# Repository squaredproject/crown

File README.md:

# Crown

This is all the code relating to the Crown burning man project of 2018.

## Crown

The Crown subdirectory is the Processing model for light control. Processing demands the name
of the directory is Crown, so Crown it is.

## model

Various design models

testing testing

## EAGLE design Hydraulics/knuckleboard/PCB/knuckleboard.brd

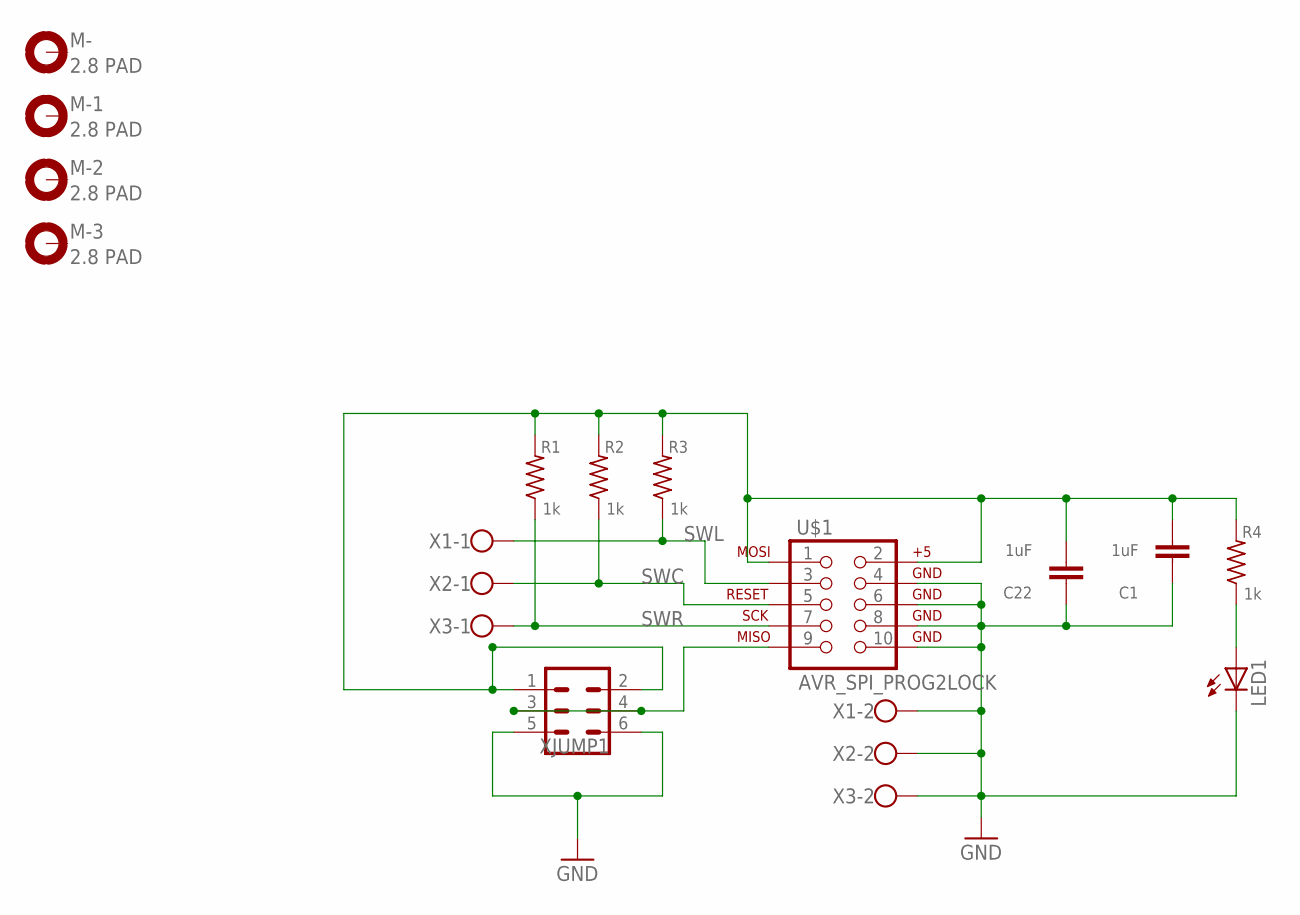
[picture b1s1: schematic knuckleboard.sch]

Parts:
C1, C22: 1uF; C1206
LED1: LEDCHIPLED_1206; CHIPLED_1206
M-, M-1, M-2, M-3: 2.8 PAD; 2,8-PAD
R1, R2, R3, R4: 1k; M1206
U$1: AVR_SPI_PROG2LOCK; 2X5-SHROUDED_LOCK
X1, X2, X3: W237-102
XJUMP1: MA03-2

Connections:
GND: C1.1, C22.1, LED1.C, U$1.4, U$1.6, U$1.8, U$1.10, X1.2, X2.2, X3.2, XJUMP1.5, XJUMP1.6
unnamed: LED1.A, R4.1
unnamed: U$1.9, XJUMP1.3, XJUMP1.4
SWC: R2.1, U$1.5, X2.1
SWL: R3.1, U$1.3, X1.1
SWR: R1.1, U$1.7, X3.1
VDD5V: C1.2, C22.2, R1.2, R2.2, R3.2, R4.2, U$1.1, U$1.2, XJUMP1.1, XJUMP1.2

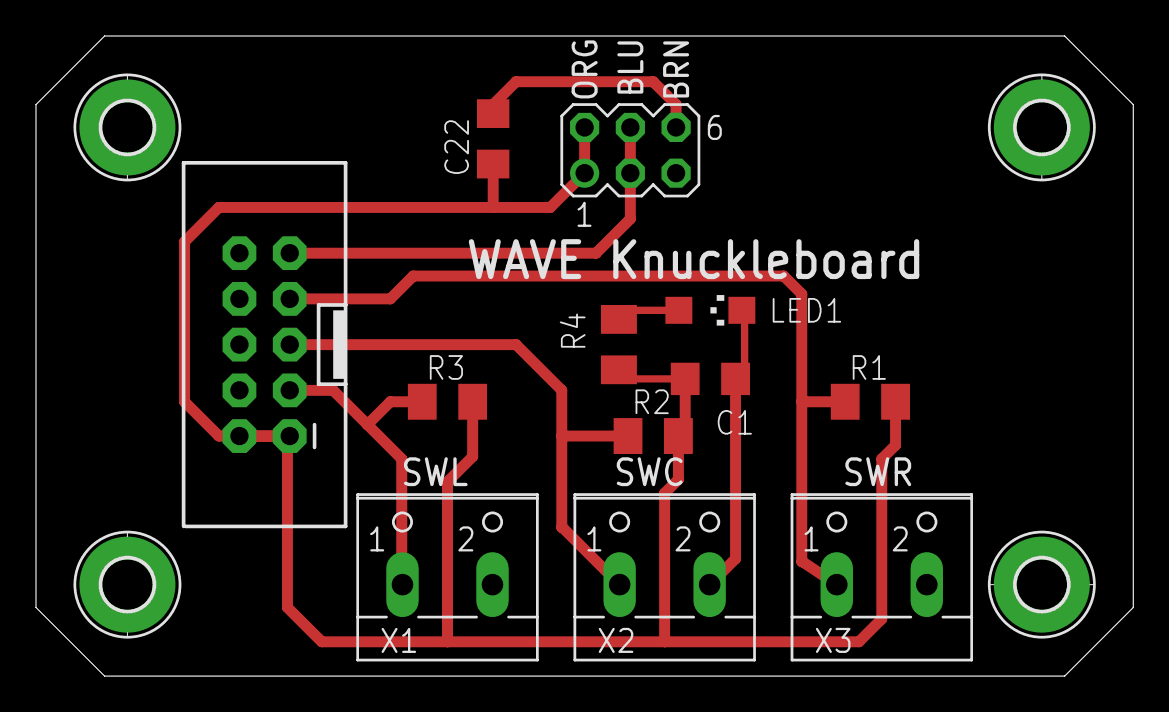
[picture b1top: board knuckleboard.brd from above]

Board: 2 copper layers, 61.0 x 35.6 mm, 16 parts (0 on the bottom side), 7 nets.

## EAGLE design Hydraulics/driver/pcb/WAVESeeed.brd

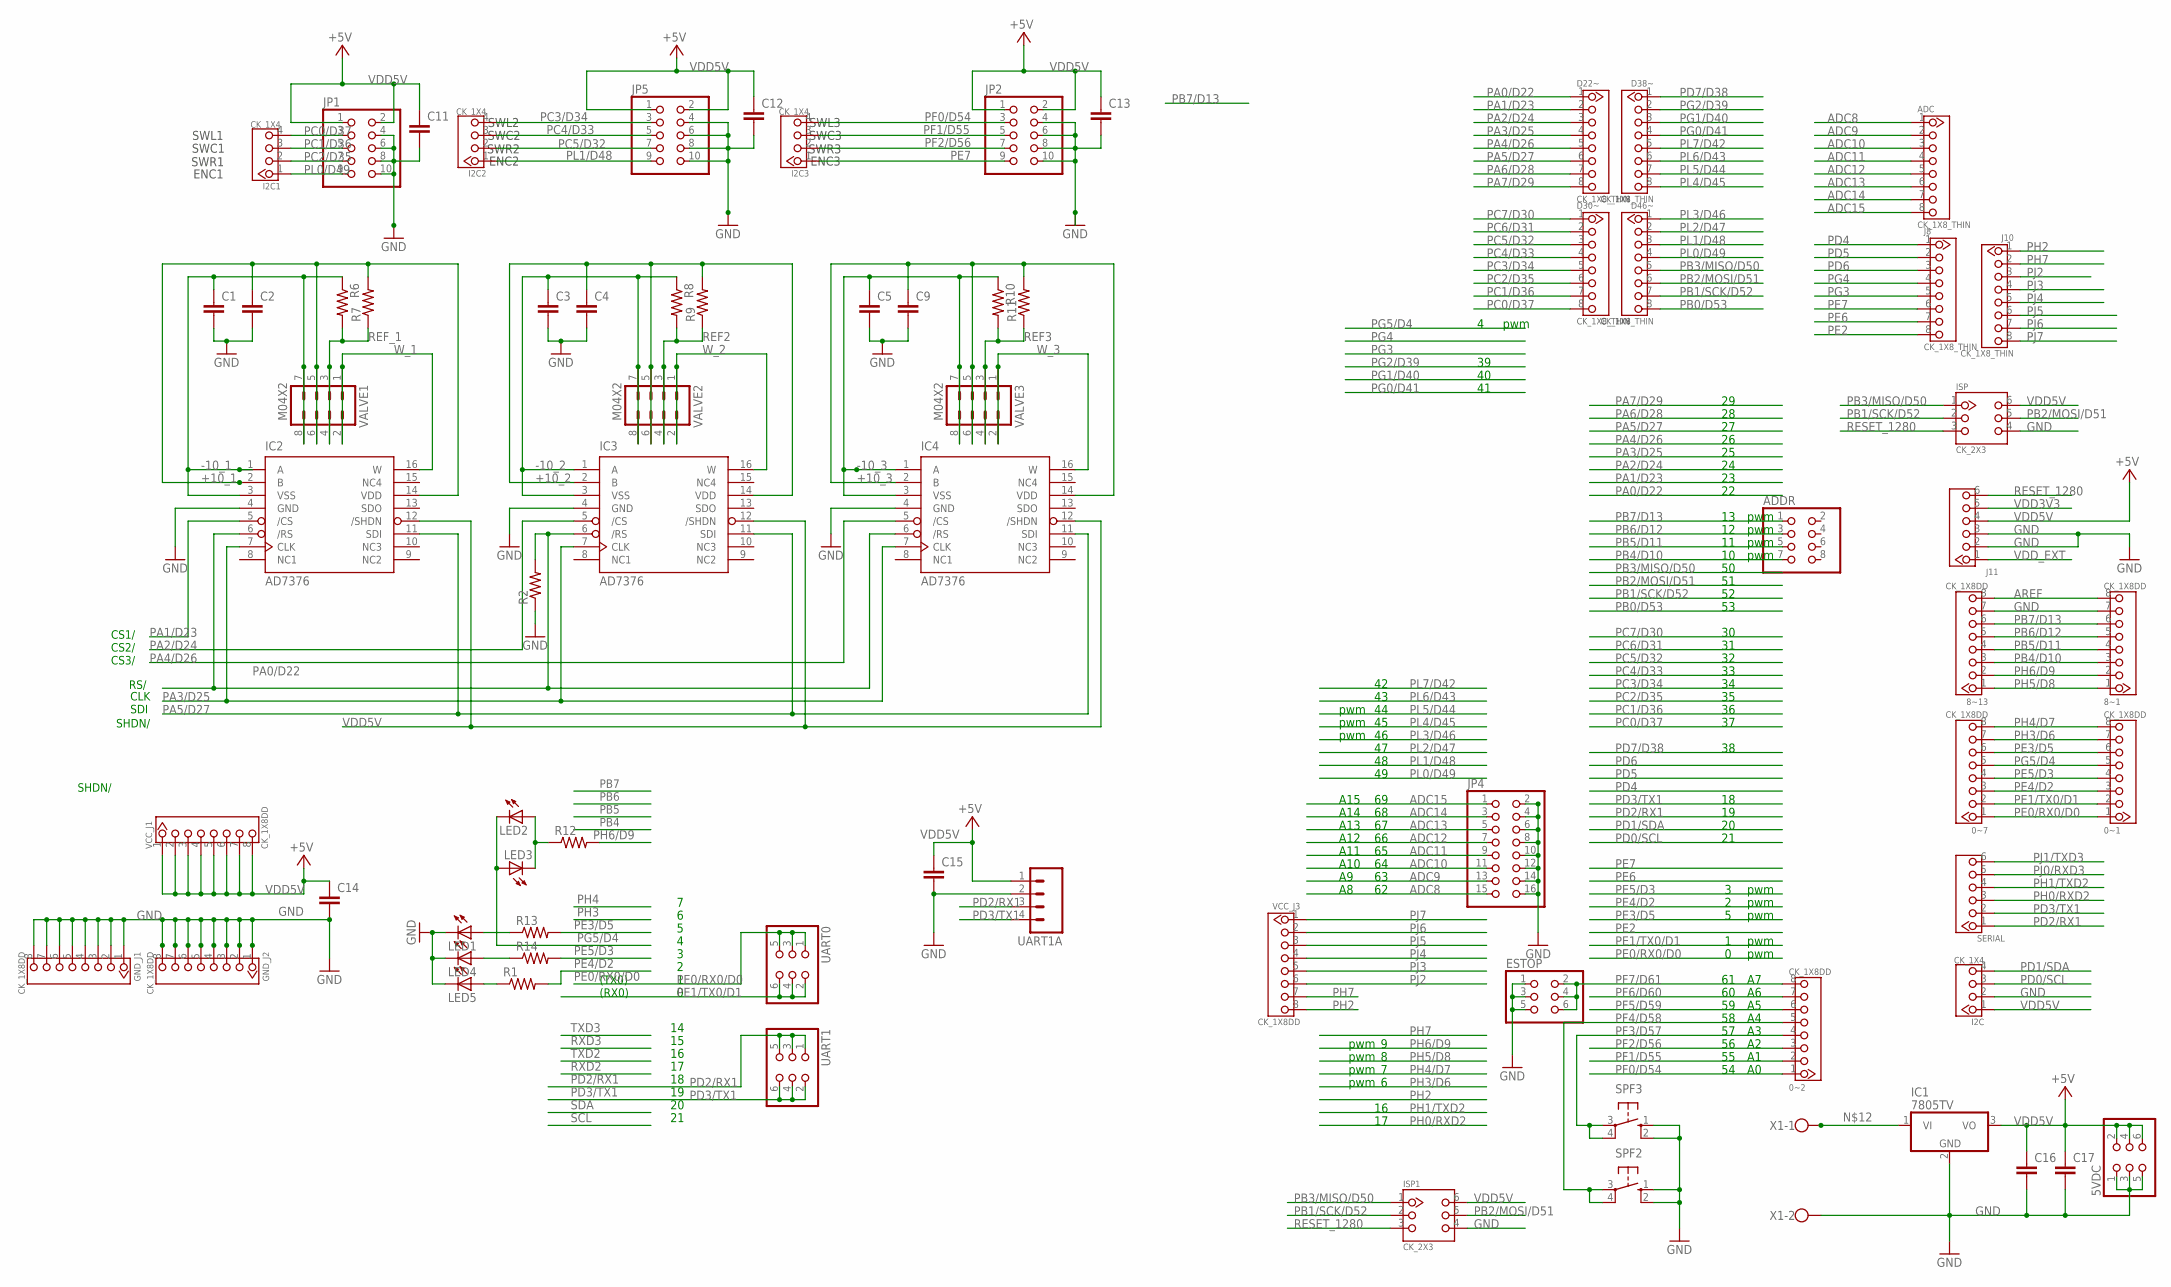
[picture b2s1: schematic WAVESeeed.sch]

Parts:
0~1, 0~2, 0~7, 8~1, 8~13: CK_1X8DD; CK_1X8
5VDC: PINHD-2X3; 2X03
ADC: CK_1X8_THIN
ADDR: PINHD-2X4; 2X04
C1, C2, C3, C4, C5, C9, C11, C15, C16: C-EUC1206; C1206
C12, C13, C14, C17: C-EUC1206K; C1206K
D22~, D30~, D38~, D46~: CK_1X8_THIN
ESTOP: PINHD-2X3; 2X03
GND_J1, GND_J2: CK_1X8DD; CK_1X8
I2C, I2C1, I2C2, I2C3: CK_1X4
IC1: 7805TV; TO220V
IC2, IC3, IC4: AD7376; SO-16W
ISP, ISP1: CK_2X3; CK_2X3_THIN
J8, J10: CK_1X8_THIN
J11: CK_1X6
JP1, JP2, JP5: PINHD-2X5; 2X05
JP4: PINHD-2X8; 2X08
LED1, LED2, LED3, LED4, LED5: LEDCHIPLED_1206; CHIPLED_1206
R1, R2, R12, R13, R14: R-US_R1206; R1206
R6, R7, R8, R9, R10, R11: R-US_M1206; M1206
SERIAL: CK_1X6
SPF2, SPF3: 10-XX; B3F-10XX
UART0, UART1: PINHD-2X3; 2X03
UART1A: M04PTH; 1X04
VALVE1, VALVE2, VALVE3: M04X2; 2X4
VCC_J1, VCC_J3: CK_1X8DD; CK_1X8
X1: W237-102

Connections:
+10_1: C2.1, IC2.2 (B), IC2.14 (VDD), R7.2, VALVE1.5, VALVE1.6
+10_2: C4.1, IC3.2 (B), IC3.14 (VDD), R9.2, VALVE2.5, VALVE2.6
+10_3: C9.1, IC4.2 (B), IC4.14 (VDD), R11.2, VALVE3.5, VALVE3.6
-10_1: C1.1, IC2.1 (A), IC2.3 (VSS), R6.1, VALVE1.7, VALVE1.8
-10_2: C3.1, IC3.1 (A), IC3.3 (VSS), R8.1, VALVE2.7, VALVE2.8
-10_3: C5.1, IC4.1 (A), IC4.3 (VSS), R10.1, VALVE3.7, VALVE3.8
ADC8: ADC.1, JP4.15
ADC9: ADC.2, JP4.13
ADC10: ADC.3, JP4.11
ADC11: ADC.4, JP4.9
ADC12: ADC.5, JP4.7
ADC13: ADC.6, JP4.5
ADC14: ADC.7, JP4.3
ADC15: ADC.8, JP4.1
AREF: 8~1.8, 8~13.8
GND: 5VDC.1, 5VDC.3, 5VDC.5, 8~1.7, 8~13.7, C1.2, C2.2, C3.2, C4.2, C5.2, C9.2, C11.2, C12.2, C13.2, C14.2, C15.2, C16.2, C17.2, ESTOP.1, ESTOP.3, ESTOP.5, GND_J1.1, GND_J1.2, GND_J1.3, GND_J1.4, GND_J1.5, GND_J1.6, GND_J1.7, GND_J1.8, GND_J2.1, GND_J2.2, GND_J2.3, GND_J2.4, GND_J2.5, GND_J2.6, GND_J2.7, GND_J2.8, I2C.2, IC1.2 (GND), IC2.4 (GND), IC3.4 (GND), IC4.4 (GND), ISP.4, ISP1.4, J11.2, J11.3, JP1.4, JP1.6, JP1.8, JP1.10, JP2.4, JP2.6, JP2.8, JP2.10, JP4.2, JP4.4, JP4.6, JP4.8, JP4.10, JP4.12, JP4.14, JP4.16, JP5.4, JP5.6, JP5.8, JP5.10, LED1.C, LED4.C, LED5.C, R2.1, SPF2.1 (S), SPF2.2 (S1), SPF3.1 (S), SPF3.2 (S1), UART1A.2, X1.2
unnamed: LED2.A, LED3.C, R12.1
unnamed: LED1.A, R13.1
unnamed: LED5.A, R1.1
unnamed: LED4.A, R14.1
unnamed: IC1.1 (VI), X1.1
PA0/D22: D22~.1, IC2.6 (/RS), IC3.6 (/RS), IC4.6 (/RS), R2.2
PA1/D23: D22~.2, IC2.5 (/CS)
PA2/D24: D22~.3, IC3.5 (/CS)
PA3/D25: D22~.4, IC2.7 (CLK), IC3.7 (CLK), IC4.7 (CLK)
PA4/D26: D22~.5, IC4.5 (/CS)
PA5/D27: D22~.6, IC2.11 (SDI), IC3.11 (SDI), IC4.11 (SDI)
PA6/D28: D22~.7
PA7/D29: D22~.8
PB0/D53: D46~.8
PB1/SCK/D52: D46~.7, ISP.2, ISP1.2
PB2/MOSI/D51: D46~.6, ISP.5, ISP1.5
PB3/MISO/D50: D46~.5, ISP.1, ISP1.1
PB4/D10: 8~1.3, 8~13.3, ADDR.7
PB5/D11: 8~1.4, 8~13.4, ADDR.5
PB6/D12: 8~1.5, 8~13.5, ADDR.3
PB7/D13: 8~1.6, 8~13.6, ADDR.1
PC0/D37: D30~.8, I2C1.4, JP1.3
PC1/D36: D30~.7, I2C1.3, JP1.5
PC2/D35: D30~.6, I2C1.2, JP1.7
PC3/D34: D30~.5, I2C2.4, JP5.3
PC4/D33: D30~.4, I2C2.3, JP5.5
PC5/D32: D30~.3, I2C2.2, JP5.7
PC6/D31: D30~.2
PC7/D30: D30~.1
PD0/SCL: I2C.3
PD1/SDA: I2C.4
PD2/RX1: SERIAL.1, UART1.1, UART1.3, UART1.5, UART1A.3
PD3/TX1: SERIAL.2, UART1.2, UART1.4, UART1.6, UART1A.4
PD4: J8.1
PD5: J8.2
PD6: J8.3
PD7/D38: D38~.1
PE0/RX0/D0: 0~1.1, 0~7.1, UART0.1, UART0.3, UART0.5
PE1/TX0/D1: 0~1.2, 0~7.2, UART0.2, UART0.4, UART0.6
PE2: J8.8
PE3/D5: 0~1.6, 0~7.6, R13.2
PE4/D2: 0~1.3, 0~7.3, R1.2
PE5/D3: 0~1.4, 0~7.4, R14.2
PE6: J8.7
PE7: I2C3.1, J8.6, JP2.9
PF0/D54: 0~2.1, I2C3.4, JP2.3
PF1/D55: 0~2.2, I2C3.3, JP2.5
PF2/D56: 0~2.3, I2C3.2, JP2.7
PF3/D57: 0~2.4, SPF3.3, SPF3.4 (P1)
PF4/D58: 0~2.5, SPF2.3, SPF2.4 (P1)
PF5/D59: 0~2.6
PF6/D60: 0~2.7
PF7/D61: 0~2.8, ESTOP.2, ESTOP.4, ESTOP.6
PG0/D41: D38~.4
PG1/D40: D38~.3
PG2/D39: D38~.2
PG3: J8.5
PG4: J8.4
PG5/D4: 0~1.5, 0~7.5, LED2.C, LED3.A
PH0/RXD2: SERIAL.3
PH1/TXD2: SERIAL.4
PH2: J10.1, VCC_J3.8
PH3/D6: 0~1.7, 0~7.7
PH4/D7: 0~1.8, 0~7.8
PH5/D8: 8~1.1, 8~13.1
PH6/D9: 8~1.2, 8~13.2, R12.2
PH7: J10.2, VCC_J3.7
PJ0/RXD3: SERIAL.5
PJ1/TXD3: SERIAL.6
PJ2: J10.3, VCC_J3.6
PJ3: J10.4, VCC_J3.5
PJ4: J10.5, VCC_J3.4
PJ5: J10.6, VCC_J3.3
PJ6: J10.7, VCC_J3.2
PJ7: J10.8, VCC_J3.1
PL0/D49: D46~.4, I2C1.1, JP1.9
PL1/D48: D46~.3, I2C2.1, JP5.9
PL2/D47: D46~.2
PL3/D46: D46~.1
PL4/D45: D38~.8
PL5/D44: D38~.7
PL6/D43: D38~.6
PL7/D42: D38~.5
REF2: R8.2, R9.1, VALVE2.3, VALVE2.4
REF3: R10.2, R11.1, VALVE3.3, VALVE3.4
REF_1: R6.2, R7.1, VALVE1.3, VALVE1.4
RESET_1280: ISP.3, ISP1.3, J11.6
VDD3V3: J11.5
VDD5V: 5VDC.2, 5VDC.4, 5VDC.6, C11.1, C12.1, C13.1, C14.1, C15.1, C16.1, C17.1, I2C.1, IC1.3 (VO), IC2.12 (/SHDN), IC3.12 (/SHDN), IC4.12 (/SHDN), ISP.6, ISP1.6, J11.4, JP1.1, JP1.2, JP2.1, JP2.2, JP5.1, JP5.2, UART1A.1, VCC_J1.1, VCC_J1.2, VCC_J1.3, VCC_J1.4, VCC_J1.5, VCC_J1.6, VCC_J1.7, VCC_J1.8
VDD_EXT: J11.1
W_1: IC2.16 (W), VALVE1.1, VALVE1.2
W_2: IC3.16 (W), VALVE2.1, VALVE2.2
W_3: IC4.16 (W), VALVE3.1, VALVE3.2

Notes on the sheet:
pwm
A10
A11
A12
A13
A14
A15
SWL1
SWC1
SWR1
ENC1
SWL2
SWC2
SWR2
ENC2
SWL3
SWC3
SWR3
ENC3
CS2/
CS3/
SDI
CLK
CS1/
SHDN/
(TX0)
(RX0)
RS/

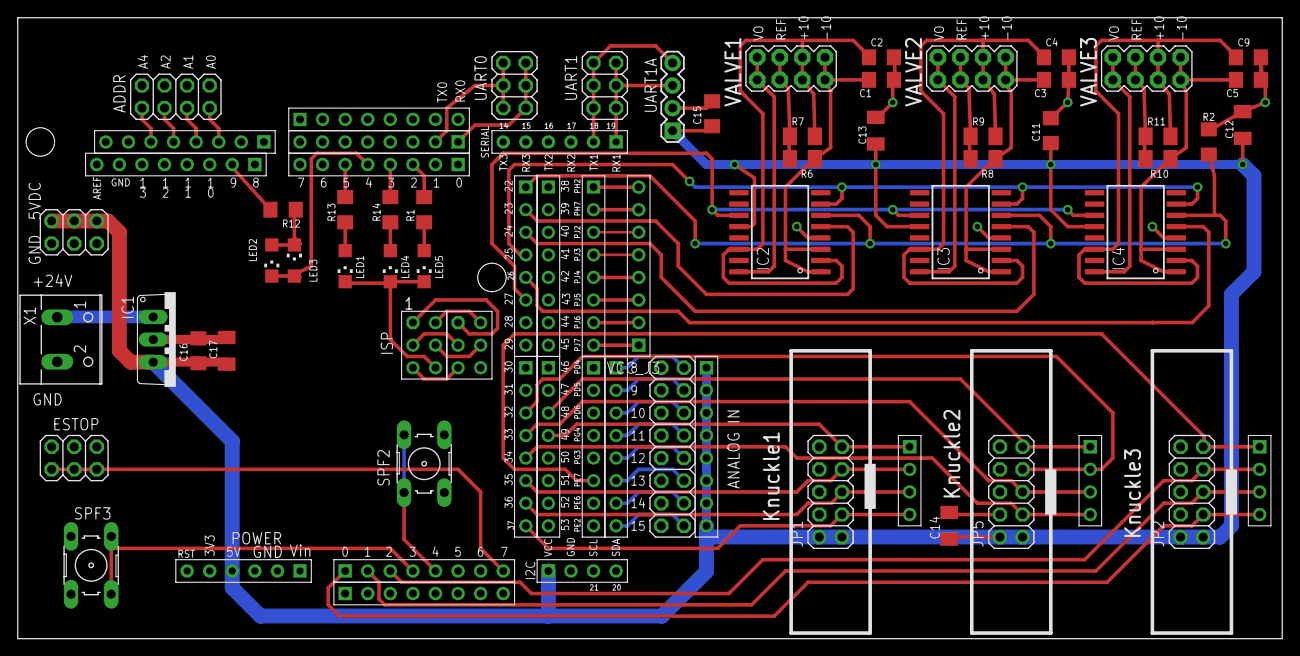
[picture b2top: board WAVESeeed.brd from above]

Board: 2 copper layers, 142.2 x 69.8 mm, 73 parts (0 on the bottom side), 77 nets.

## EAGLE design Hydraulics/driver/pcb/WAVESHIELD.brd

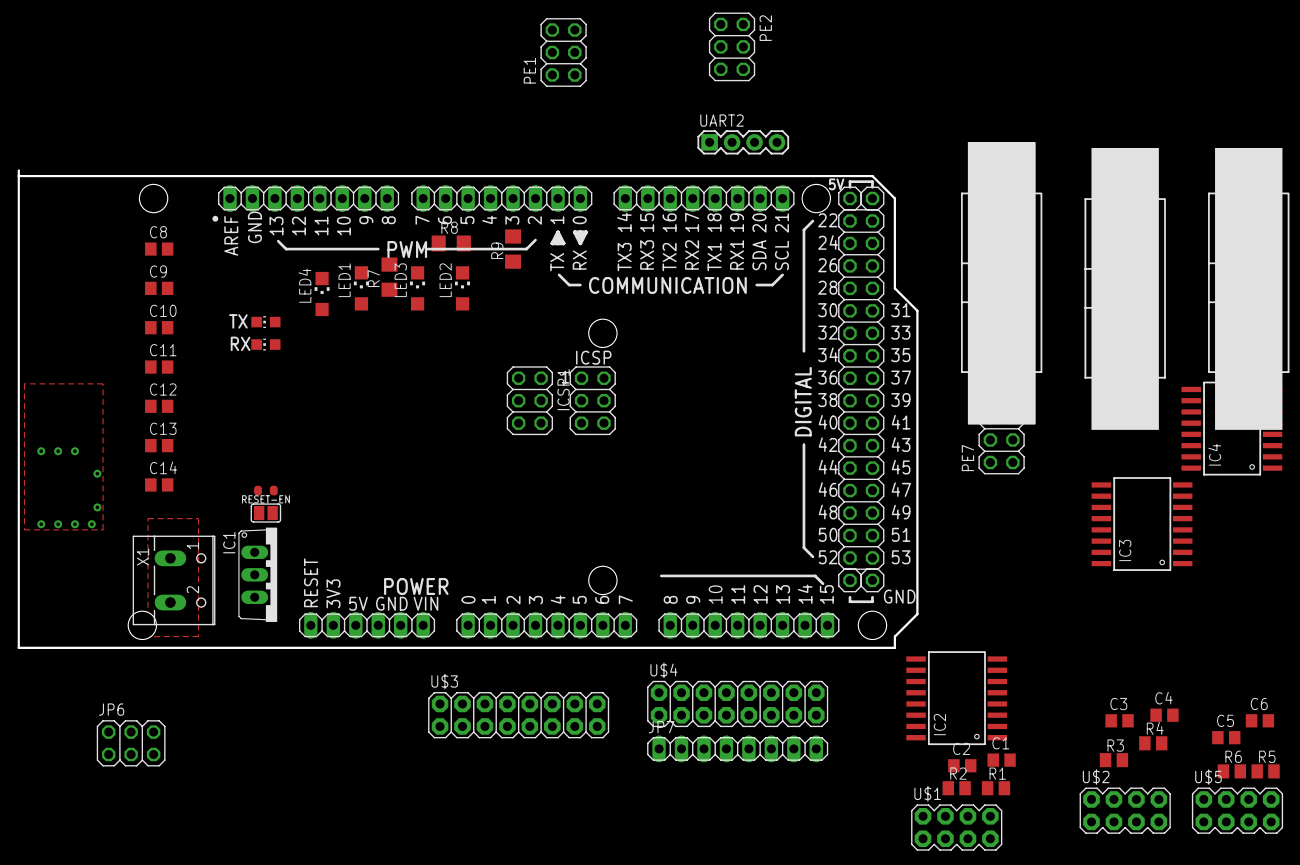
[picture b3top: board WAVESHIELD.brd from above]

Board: 2 copper layers, 101.6 x 54.0 mm, 64 parts (1 on the bottom side), 63 nets.

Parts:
C1, C2, C3, C4, C5, C6, C8, C9, C10, C11, C12, C13, C14: C0805
C7: 100n; C0603-ROUND
COMMUNICATION: 1X08
IC1: 7805TV; TO220V
IC2, IC3, IC4: AD7376; SO-16W
ICSP, ICSP1: ICSP; 2X03
JP1, JP2, JP3, JP4: 1X01
JP6: 2X03
JP7: 1X08
KNUCK1, KNUCK2, KNUCK3: M05X2SHD_LOCK; 2X5-SHROUDED_LOCK
LED1, LED2, LED3, LED4: CHIPLED_1206
PE1, PE2, PE7: 2X03
PORTF: 1X08
PORTL: 1X08
POWER: 1X06
PWMH: 1X08
PWML: 1X08
R1, R2, R3, R4, R5, R6: M0805
R7, R8, R9: R1206
RESET-EN: SJ
RX: YELLOW; CHIP-LED0805
TX: YELLOW; CHIP-LED0805
U$1, U$2, U$5: M04X2; 2X4
U$3, U$4: M08X2; 2X8
UART2: 1X04
UBOOT: SJ
X1: W237-102
XIOH: 2X08
XIOL: 2X08

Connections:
+5V: C8.1, C9.1, C10.1, C12.1, C13.1, IC1.3, ICSP.2, ICSP1.2, JP1.1, JP2.1, JP7.1, JP7.2, JP7.3, JP7.4, JP7.5, JP7.6, JP7.7, JP7.8, KNUCK1.1, KNUCK1.2, KNUCK2.1, KNUCK2.2, KNUCK3.1, KNUCK3.2, POWER.3
ADC8: PORTL.1, U$4.2
ADC9: PORTL.2, U$4.4
ADC10: PORTL.3, U$4.6
ADC11: PORTL.4, U$4.8
ADC12: PORTL.5, U$4.10
ADC13: PORTL.6, U$4.12
ADC14: PORTL.7, U$4.14
ADC15: PORTL.8, U$4.16
DTR: C7.1, UBOOT.1
GND: C1.2, C2.2, C3.2, C4.2, C5.2, C6.2, C8.2, C10.2, C12.2, C13.2, IC1.2, IC2.4, IC3.4, IC4.4, ICSP.6, ICSP1.6, JP3.1, JP4.1, KNUCK1.4, KNUCK1.6, KNUCK1.8, KNUCK1.10, KNUCK2.4, KNUCK2.6, KNUCK2.8, KNUCK2.10, KNUCK3.4, KNUCK3.6, KNUCK3.8, KNUCK3.10, LED1.C, LED4.C, PE7.1, PE7.3, PE7.5, POWER.4, POWER.5, PWMH.7, U$3.2, U$3.4, U$3.6, U$3.8, U$3.10, U$3.12, U$3.14, U$3.16, U$4.15, UART2.2, UBOOT.2, X1.2
unnamed: LED2.A, LED3.C, R7.1
unnamed: LED1.A, R8.1
unnamed: LED4.A, R9.1
unnamed: PE1.2, PE1.4, PE1.6
unnamed: C1.1, IC2.1, IC2.3, R1.1, U$1.7, U$1.8
unnamed: IC1.1, X1.1
unnamed: R1.2, R2.1, U$1.3, U$1.4
unnamed: IC2.16, U$1.1, U$1.2
unnamed: C3.1, IC3.1, IC3.3, R3.1, U$2.7, U$2.8
unnamed: C4.1, IC3.2, R4.2, U$2.5, U$2.6
unnamed: R3.2, R4.1, U$2.3, U$2.4
unnamed: IC3.16, U$2.1, U$2.2
unnamed: C5.1, IC4.1, IC4.3, R5.1, U$5.7, U$5.8
unnamed: C6.1, IC4.2, R6.2, U$5.5, U$5.6
unnamed: R5.2, R6.1, U$5.3, U$5.4
unnamed: IC4.16, U$5.1, U$5.2
PA0: IC2.12, IC3.12, IC4.12, XIOH.16
PA1: IC2.5, XIOH.15
PA2: IC3.5, XIOH.14
PA3: IC2.7, IC3.7, IC4.7, XIOH.13
PA4: IC4.5, XIOH.12
PA5: IC2.11, IC3.11, IC4.11, XIOH.11
PB1: ICSP.3, ICSP1.3, XIOL.2
PB2: ICSP.4, ICSP1.4, XIOL.3
PB3: ICSP.1, ICSP1.1, XIOL.4
PC0: KNUCK1.3, XIOH.1
PC1: KNUCK1.5, XIOH.2
PC2: KNUCK1.7, XIOH.3
PC3: KNUCK2.3, XIOH.4
PC4: KNUCK2.5, XIOH.5
PC5: KNUCK2.7, XIOH.6
PE1: PE1.1, PE1.3, PE1.5, PWML.2
PE3: PWML.6, R8.2
PE5: PWML.4, R9.2
PE7/ICP3: KNUCK3.9, PE7.2, PE7.4, PE7.6
PF0: KNUCK3.3, PORTF.1, U$3.1
PF1: KNUCK3.5, PORTF.2, U$3.3
PF2: KNUCK3.7, PORTF.3, U$3.5
PF3: PORTF.4, U$3.7
PF4: PORTF.5, U$3.9
PF5: PORTF.6, U$3.11
PF6: PORTF.7, U$3.13
PF7: PORTF.8, U$3.15
PG5: LED2.C, LED3.A, PWML.5
PH6: PWMH.2, R7.2
PL0: KNUCK1.9, XIOL.5
PL1: KNUCK2.9, XIOL.6
RESET: C7.2, ICSP.5, ICSP1.5, POWER.1, RESET-EN.1, RESET-EN.2
RXD1: COMMUNICATION.3, PE2.2, PE2.4, PE2.6
TXD1: COMMUNICATION.4, PE2.1, PE2.3, PE2.5, UART2.3
VALVE1: C2.1, IC2.2, IC2.14, R2.2, U$1.5, U$1.6
VDD: IC3.14, IC4.14

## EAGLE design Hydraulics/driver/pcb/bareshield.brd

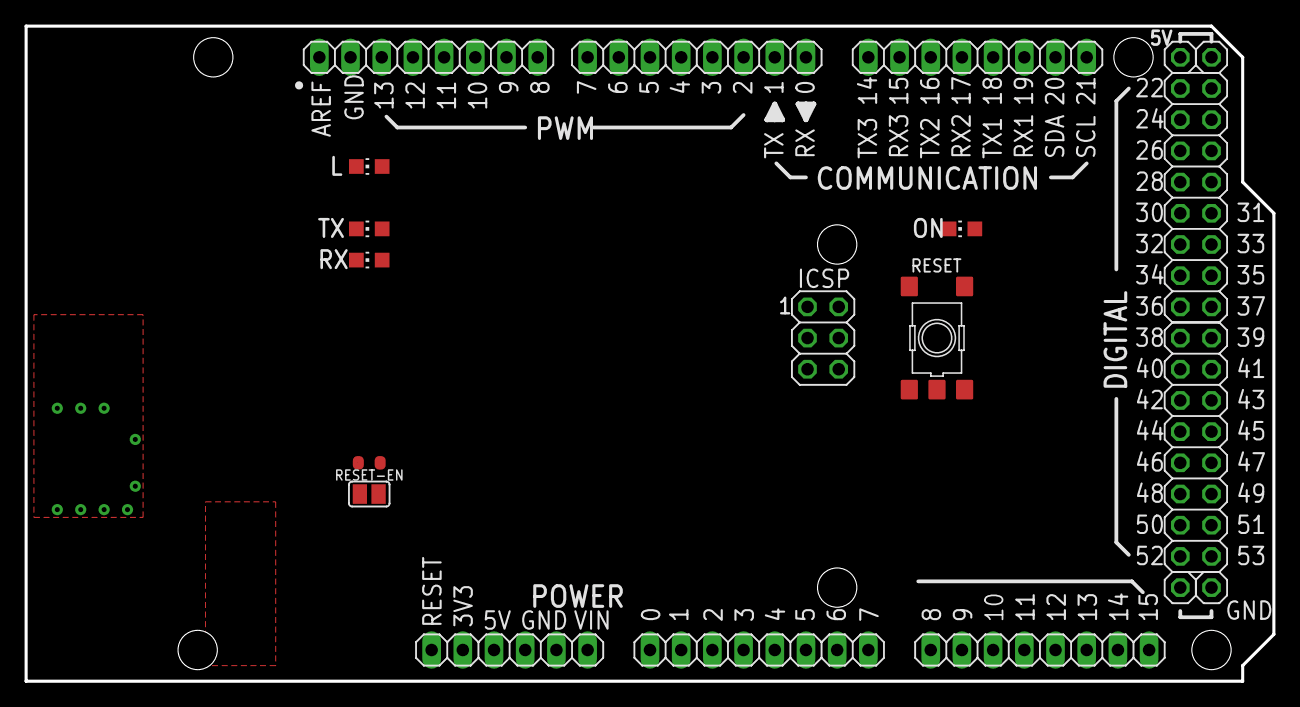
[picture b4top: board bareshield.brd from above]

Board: 2 copper layers, 101.6 x 53.3 mm, 21 parts (1 on the bottom side), 7 nets.

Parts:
ADCH: 1X08
ADCL: 1X08
C7: 100n; C0603-ROUND
COMMUNICATION: 1X08
ICSP: ICSP; 2X03
JP1, JP2, JP3, JP4: 1X01
L: YELLOW; CHIP-LED0805
ON: GREEN; CHIP-LED0805
POWER: 1X06
PWMH: 1X08
PWML: 1X08
RESET: TS42
RESET-EN: SJ
RX: YELLOW; CHIP-LED0805
TX: YELLOW; CHIP-LED0805
UBOOT: SJ
XIOH: 2X08
XIOL: 2X08

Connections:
+5V: ICSP.2, JP1.1, JP2.1, POWER.3
DTR: C7.1, UBOOT.1
GND: ICSP.6, JP3.1, JP4.1, L.C, ON.C, POWER.4, POWER.5, PWMH.7, RESET.1, RESET.2, UBOOT.2
PB1: ICSP.3, XIOL.2
PB2: ICSP.4, XIOL.3
PB3: ICSP.1, XIOL.4
RESET: C7.2, ICSP.5, POWER.1, RESET.3, RESET.4, RESET-EN.1, RESET-EN.2

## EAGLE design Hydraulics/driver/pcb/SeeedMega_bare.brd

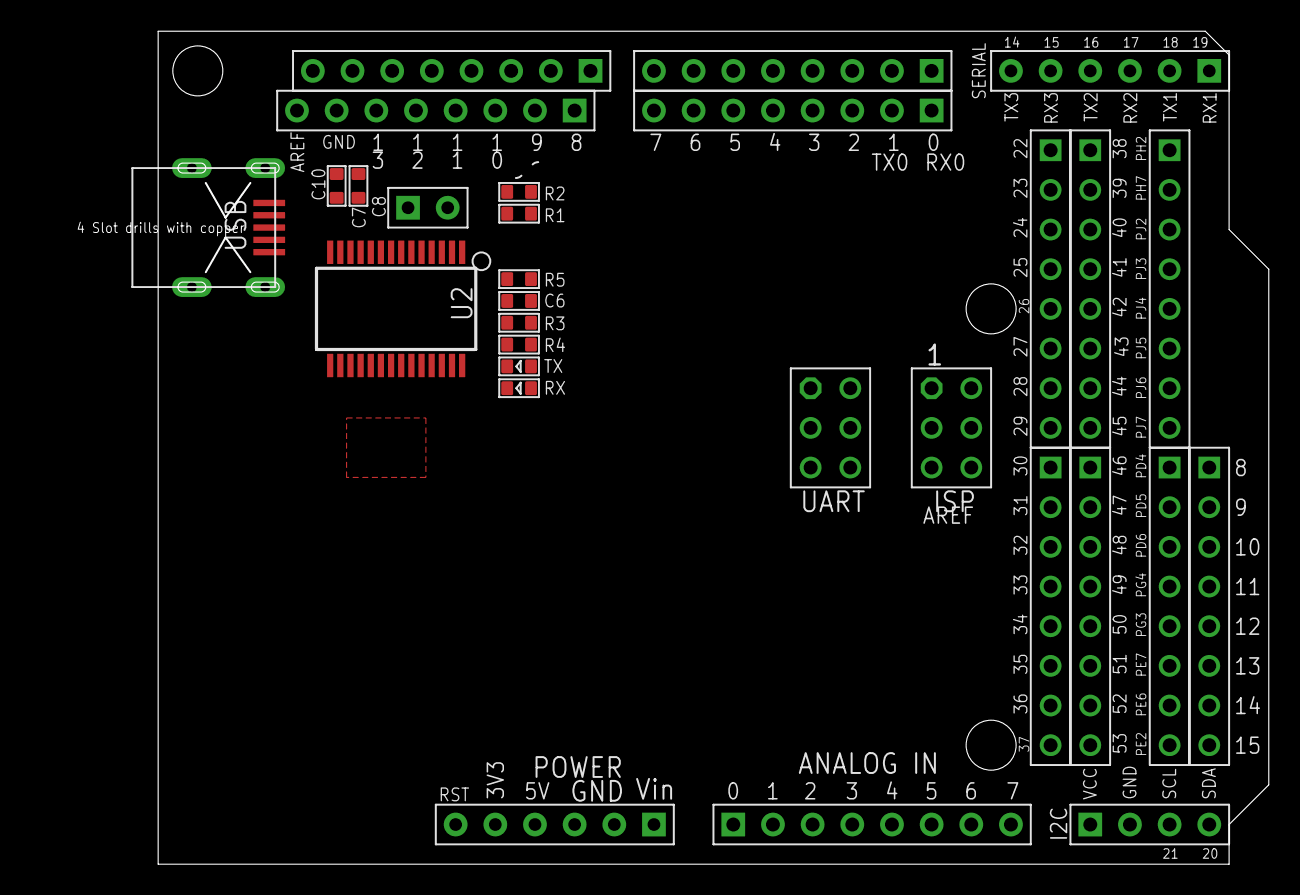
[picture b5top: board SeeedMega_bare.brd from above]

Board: 2 copper layers, 71.1 x 53.3 mm, 30 parts (0 on the bottom side), 37 nets, no tracks yet.

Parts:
0~1, 0~2, 0~7, 8~1, 8~13: CK_1X8DD; CK_1X8
C6, C7: 100n; 0603_S
C8: PWR2P_2.54_180; PWR_1X2
C10: 10n; 0603_S
D22~, D30~, D38~, D46~: CK_1X8_THIN
I2C: CK_1X4
ISP: CK_2X3; CK_2X3_THIN
J8, J9, J10: CK_1X8_THIN
J11: CK_1X6@1
R1, R2, R3, R4: 1k; 0603_S
R5: 10k; 0603_S
RX: LED0603; LED0603_S
SERIAL: CK_1X6@1
TX: LED0603; LED0603_S
U2: FT232RL; SSOP28
UART: CK_2X3; CK_2X3_THIN
USB: MINI_STRONG

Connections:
AREF: 8~1.8, 8~13.8
CTS: U2.11, UART.3
D+: U2.15, USB.3
D-: U2.16, USB.2
DCD: U2.10, UART.4
DSR: U2.9, UART.2
DTR: U2.2, UART.6
FT_RST: C6.2, R5.2, U2.19
FT_RX: R2.1, U2.5
FT_TX: R1.1, U2.1
GND: 8~1.7, 8~13.7, C6.1, C7.2, C8.-, C10.1, I2C.2, ISP.4, J11.2, J11.3, U2.7, U2.18, U2.21, U2.25, U2.26, USB.5, USB.GND@1, USB.GND@2, USB.GND@3, USB.GND@4
LED_RX: RX.2, U2.23
LED_TX: TX.2, U2.22
unnamed: R3.1, RX.1
unnamed: R4.1, TX.1
PB1/SCK/D52: D46~.7, ISP.2
PB2/MOSI/D51: D46~.6, ISP.5
PB3/MISO/D50: D46~.5, ISP.1
PB4/D10: 8~1.3, 8~13.3
PB5/D11: 8~1.4, 8~13.4
PB6/D12: 8~1.5, 8~13.5
PB7/D13: 8~1.6, 8~13.6
PE0/RX0/D0: 0~1.1, 0~7.1, R1.2
PE1/TX0/D1: 0~1.2, 0~7.2, R2.2
PE3/D5: 0~1.6, 0~7.6
PE4/D2: 0~1.3, 0~7.3
PE5/D3: 0~1.4, 0~7.4
PG5/D4: 0~1.5, 0~7.5
PH3/D6: 0~1.7, 0~7.7
PH4/D7: 0~1.8, 0~7.8
PH5/D8: 8~1.1, 8~13.1
PH6/D9: 8~1.2, 8~13.2
RESET_1280: ISP.3, J11.6
RI: U2.6, UART.5
RTS: U2.3, UART.1
VCC: I2C.1, ISP.6, U2.4
VDD5_USB: C7.1, C8.+, C10.2, R3.2, R4.2, R5.1, U2.20, USB.1

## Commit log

2018-07-23 Adding empty files to make the repo not empty
2018-07-23 Initial checkin
2018-07-23 Checkin of one of the models
2018-07-23 Better directory structure
2018-07-24 Rename directory because Crown is picky
2018-07-24 Switch default output to NDB
2018-07-24 Remove the NFC code, not used for the project
2018-07-24 Get the fence IP properly assigned to the parent
2018-07-24 check in existing conductor code
2018-07-24 initial commit of existing driver code
2018-07-24 initial check in of existing pcb and related materials for driver
2018-07-24 add existing knuckleboard pcbs
2018-07-24 initial check in of maquette code
2018-07-24 minor cleanups
2018-07-25 moving ino file to be arduino ide friendly
2018-07-27 Remove more of NFC which will not be used in this project
2018-07-27 Added back in the test pattern, although it's not a very pretty pattern. Next: make pretty.
2018-07-27 Put in a simple T1 pattern that lights every bulb in the string Still thinking about how T2 can light the different strands
2018-07-27 Test two, which is strand by strand, is pretty reasonable.
2018-07-27 Mostly formatting. Changing some output string formats as well
2018-07-27 adding buttons, modes, reading from serial port. Basic testing done, seems to work
2018-07-30 Resize to inches which makes patterns look better
2018-08-01 Add the missing run.sh so it can run headless.
2018-08-01 Allow gradle builds
2018-08-01 Fix recursive problem in gradle build
2018-08-02 Jars and libraries for Launchpad midi controller
2018-08-02 Changed model to use 6 NDB instead of 5, thus avoiding problem with large UDP sizes
2018-08-04 checking in makefile for conductor
2018-08-04 update maquette code. Teaching it Canbus
2018-08-04 adding tar'd canbus library
2018-08-04 Move the canbus somplace a little more sensible
2018-08-04 Update to the 6 NDB descriptionwq
2018-08-06 changes to make 485 bus work better
2018-08-07 change ordering of joints to match new boxes. Add better cleanup for homing code. Add running flag (not set initially)
2018-08-11 Better hello world, prints the button locations
2018-08-11 Added information about Midi
2018-08-11 Remove these old cluster files
2018-08-11 updated compile/run scripts to use new gradle build system and classpath
2018-08-11 added how to run info to readme
2018-08-12 Making the Launchpad work. Also removed vestigates of the ipad and the nfc tags
2018-08-13 Add canbus library, and C wrapper Note: A few scary things here, like starting to define the HZ macro
2018-08-13 Change startup playlist to be a config option
2018-08-13 Update the instructions on how to save a set
2018-08-15 APC40 now functional
2018-08-17 updated compile/run to use gradle added systemctl service file for running crown software on startup on odroid
2018-08-17 made run command work on odroid
2018-08-17 added more info to readme
2018-08-17 added info about changing NDB ip address
2018-08-17 Send packets by default in headless mode
2018-08-17 Create new config for whether to startup with LiveOutput enabled or not
2018-08-17 Change default for send packets to 0
2018-08-17 Triggers are happening, X and Y seem reversed
2018-08-18 A set of java midi libraries for macos that don't suck or suck less
2018-08-18 Removing the old mmj jar,
2018-08-18 Remove the mac specific APC libraries because we have core4j now
2018-08-18 Actually remove these troublesome mmj jar things now that we have core working
2018-08-18 Make the fence patterns not display by default, so you can save CPU
2018-08-18 Updated to working version of pattern file ;
2018-08-18 Not sure why this is more up to date but we'll be using it
2018-08-18 That was high level of difficulty. Was not receiving noteOff from LX because of a typing problem.
2018-08-18 More sysex fun
2018-08-19 Just fixed some whitespace
2018-08-19 Init the effects, otherwise they don't work
2018-08-22 make the canbus stuff work
2018-08-22 Get CAN bus working. Translation of commands from RPI over the serial port. Initial LED and pose code
2018-08-22 Initial check in for rpi control code
2018-08-22 The simplest rotating pattern I can think of. Will improve...
2018-08-23 A more throbby rotating pattern
2018-08-24 Colin's COol Pattern
2018-08-25 Running as a service, added
2018-08-26 addl mods - not done yet, need to get to another computer
2018-09-05 Minor changes to make conductor work with current driver code, and be a little faster. Changed indexing on fingers to be 1 based in command to driver. Changed cpu in makefile to 2560 - which is the a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
2018-09-05 Additions and fixups on playa. More sophistication dealing with homing issues - note that at this point we\'re giving up on automatic homing because of the unreliability of the switches, but this cod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
2018-09-05 Attempts on playa to get maquette UI working, at least well enough to handle simple homing tasks. Note that this code is *not* even close to production quality - it\'s simply as far as I got before t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
2018-09-13 Add one extra pattern, a color strobe
2018-09-13 Fix multithread, others
2018-09-23 Playlists that were made on the playa
2018-09-23 Make it clear that's the old squared playlist not any that were made on the playa specifically for Crown
2018-09-23 Last minute launchpad changes
2018-10-20 Fixups for maquette. Allow enable/disable of joints. Make pose mode work. Other assorted bug fixes
2018-10-21 Fix problem where the default set list was corrupt in some way
2023-02-05 adding some installation breadcrumbs for rpi
2023-02-07 fix up debugging statements on maquette arduino
2023-02-07 add canonical conversions - not used yet though
2023-02-07 stupid test for git pushing to github
2023-02-13 Fixups for crown serial. Still sucks, but opens correct port, doesnt fail select on write queue. Should be some way of integrating write queue with select, and this should be running in its own proce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
2023-02-13 Refactor of crown.py. Made python3 compatible, change to Flask webserver, encapsulated some of the request/response in classes. Throughput tested with simple maquette command <ms> (maquette status), 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
2023-02-14 Fixups for basic maquette functionality. Make sure parsing works correctly, send correct json, dont automatically retry
2023-02-14 Add ability to print canonical values, avoid overwrite on long status response
2023-02-24 Save and restore configuration data from EEPROM. Start of work to make protocol between arduino and rpi more sane
2023-02-24 changing default range for maquette to better match actual. Still will probably need to set joint range manually. Move to canonical values as standard for joint position at this level
2023-02-25 get http requests running correctly modulo needed refactoring
2023-02-25 Get website working under Flask, enable some of the maquette controls
2023-02-28 fixups to get web control page working. Slight rework of asyncRequestor to handle arguments, fix some formatting on responses, prevent closures in javascript from evaluating too early. There's still 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
2023-02-28 Reworked button and pose code, make more object oriented, solidify interfaces and state machine
2023-03-04 styling up the ui
2023-03-04 adding tower position images, more styling
2023-03-07 Adding ability to turn on and off joints in software. Minor cleanup. All changes in the driver section. NB - changes to CAN_message not moved to maquette!
2023-03-07 make driver build on my machine again - and fix typos that I added in the last check in
2023-03-07 adding missing images from jquery
2023-03-08 extremely minor edits bringing in the line or two of lost 2018 code that I want to revive
2023-03-08 adding shared folder because the protocol I'm using with CAN is defined in two places
2023-03-08 making rpi and web portions of tower controls working - can calibrate tower, enable disable towers and joints. No position setting yet, no modes
2023-03-10 manual, canonical positioning from the UI
2023-03-10 sculpture control ui fixups
2023-04-24 apply clang-format to c files
2023-04-24 apply black to py files
2023-04-26 safety module integration with motion
2023-04-26 Creating new section of repo for the control box code - there are a lot of duplications still
2023-04-26 filename change to allow arduino toolchain to work. Minor compilation error - code now downloads and doesnt immediately crash on mega
2023-04-27 switch works. Started work of separating out maquette from controller - not done yet...
2023-04-27 adding UART0 and 2 modules to controller. Note that these are identical to the ones in the conductor, and we should standardize the location. I think there are four copies now
2023-04-27 fixup c++/c compilation incompatibilities with UART modules
2023-04-27 cleanups - getting ready for testing
2023-04-27 Set switch pin to match wiring and physical switch
2023-04-27 implemented simple safety mechanism - but uses floating point and probably is not very performant
2023-04-27 starting to come back through maquette to integrate with controller
2023-04-28 WIP - maquette relay data on rpi
2023-04-28 Getting the relay system working... mostly
2023-04-28 breadcrumbs in how to download onto the driver board
2023-04-28 changed name, minor tweak to Recording
2023-04-28 Relay from maquette working
2023-04-28 fixups to allow relay to grab data from crown serial
2023-04-28 adding relay to hydraulics main
2023-04-29 Update makefile to include the location of arduino libraries that are easier to find
2023-04-29 Check in the canbus libraries that are found on the RPI. To memory, these were taken from somewhere and mashed about a bit by bbb... or maybe these are stock...
2023-04-29 canonical values in fixed point, do not send canonical values unless #define. Also make forcing run/home/center easier
2023-04-30 more fixups for canonical values, relay
2023-04-30 upload and compile scripts, pt1
2023-04-30 incorporate brians fixes to command buffer, minor naming changes
2023-04-30 Fix bug in CrownSerial overflow reporting
2023-04-30 final bit of relay - careful about multiprocessing, careful about not overloading serial queues when enet is backed up
2023-04-30 Fixed stack overflows and 0 and 1 index confusion in towers Seems more reliable now
2023-06-25 fixups to get sculpture web interface working
2023-06-25 Updates to get maquette working
2023-06-25 fixups to relay and logging
2023-06-25 fixing relay... and not creating extra locks and queues
2023-06-26 Make the parser printing more useful
2023-06-26 Log rotation for the controller
2023-07-01 debug rework, print CAN errors, reduce sizes of buffers, make CAN status command return correct command id
2023-07-01 fixups for relay
2023-07-01 make rotating log handler work
2023-07-01 fixup name of log file
2023-07-02 do not block on individual tower response when doing sculpture get status
2023-07-02 adding ability to move tower to center position
2023-07-02 add button to manually refresh tower status
2023-07-02 canvas changes
2023-07-02 fixups for rendering tower info
2023-07-02 minor rendering cleanups
2023-07-02 remove excess parameters
2023-07-02 make option changes on towers display correctly
2023-07-02 style unresponding towers
2023-07-02 fixups for sending target position values
2023-07-02 easier to read string
2023-07-02 enable CAN bus
2023-07-03 adding rotating loggers on maquette
2023-07-03 Maquette relay improvements - listen for mode change, better shutdown
2023-07-03 fixup running and center in UI
2023-07-03 minor printing cleanups
2023-07-03 attempting to clear serial port on open
2023-07-03 damn the comments
2023-07-04 adding utility for playing with PID values
2023-07-04 make PID set work from html call
2023-07-04 UI fixups
2023-07-04 adding ability to see and clear hw errors
2023-07-04 additional debug for problem with status not displaying - commands can eat the results of other commands
2023-07-04 cleaning up logging and serial on maquette
2023-07-04 upload and compile scripts for mega
2023-07-04 Changed to a more pleasing installation of java, and update the exec flag
2023-07-05 Allow joint software enable/disable. CAN cleanups
2023-07-05 swap conductor and manual pin so that manual is in the center. Sanity and safety
2023-07-05 update firmware version

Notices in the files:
parts and their libraries:
SparkFun-Connectors: Licensing: CC v3.0 Share-Alike You are welcome to use this library for commercial purposes.
SparkFun-Aesthetics: Released under the Creative Commons
SparkFun-Aesthetics: http://creativecommons.org/licenses/by-sa/3.0
